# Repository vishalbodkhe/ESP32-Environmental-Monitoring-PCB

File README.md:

# ESP32 Environmental Monitoring PCB

A custom 2-layer PCB designed in KiCad for an ESP32-based environmental monitoring system.

## Features

- ESP32-WROOM-32
- DHT11 temperature and humidity sensor
- OLED I2C display
- LDR light sensor
- 5V USB power input
- AMS1117-3.3V regulation
- Reset and Boot buttons
- Power LED
- 4 × M3 mounting holes
- GND copper zone
- Custom PCB routing
- DRC verified
- Manufacturing-ready Gerber and drill files

## Hardware

| Component | Function |
|---|---|
| ESP32-WROOM-32 | Main Controller |
| DHT11 | Temperature & Humidity |
| LDR | Light Detection |
| OLED | I2C Display |
| AMS1117-3.3 | 5V to 3.3V Regulation |
| USB | Power Input |

## ESP32 Connections

| ESP32 Pin | Function |
|---|---|
| GPIO4 | DHT11 Data |
| GPIO21 | OLED SDA |
| GPIO22 | OLED SCL |
| GPIO34 | LDR ADC |
| GPIO0 | Boot |
| EN | Reset |

## Design Tools

- KiCad
- Schematic Editor
- PCB Editor
- 3D Viewer
- Gerber Viewer

## PCB Design

The PCB was designed as a 2-layer board with a dedicated GND copper zone, custom routing, antenna keep-out area and four M3 mounting holes.

## Manufacturing

Gerber and PTH/NPTH drill files are included for PCB manufacturing.

## Project Images

## Author

**Vishal Bodkhe**

Electronics & Computer Engineering

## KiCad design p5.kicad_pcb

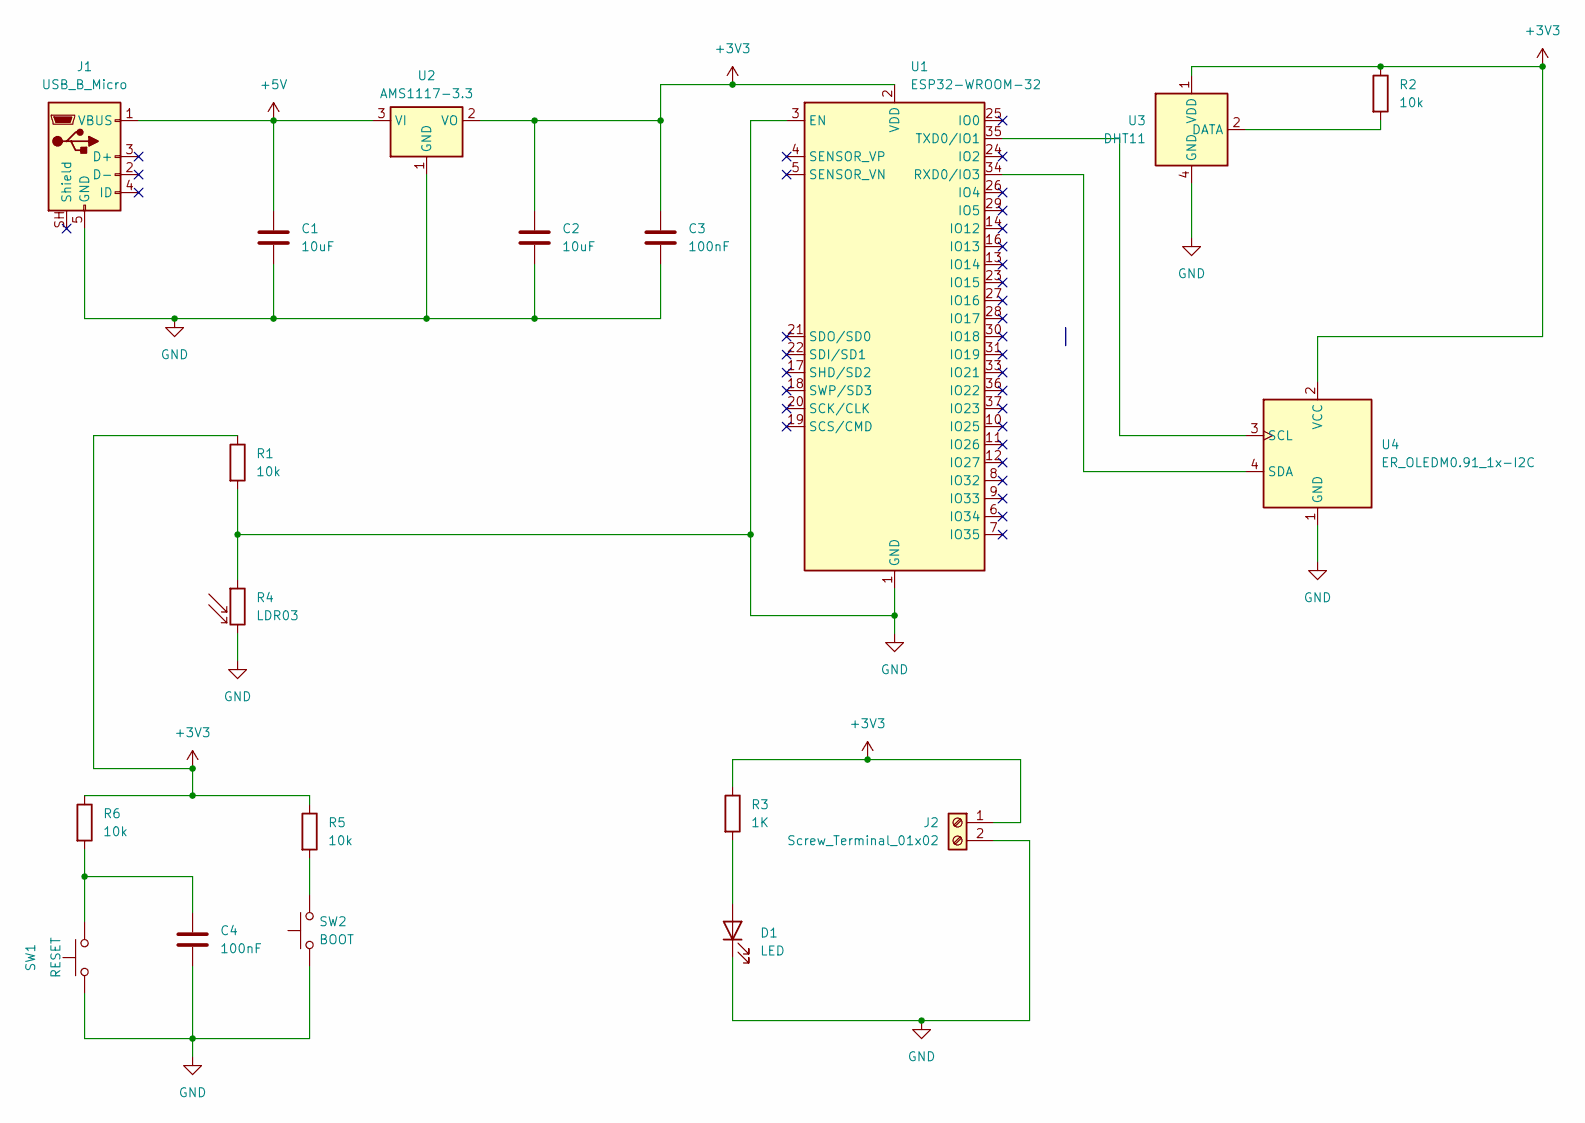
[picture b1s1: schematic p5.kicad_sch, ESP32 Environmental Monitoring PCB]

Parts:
C1, C2: 10uF; C_0805_2012Metric
C3, C4: 100nF; C_0805_2012Metric
D1: LED; LED_D5.0mm
J1: USB_B_Micro; USB_Micro-B_Molex-105017-0001
J2: Screw_Terminal_01x02; PinHeader_1x02_P2.54mm_Vertical
R1, R2, R5, R6: 10k; R_0805_2012Metric
R3: 1K; R_0805_2012Metric
R4: LDR03; R_LDR_10x8.5mm_P7.6mm_Vertical
SW1: RESET; SW_PUSH_6mm
SW2: BOOT; SW_PUSH_6mm
U1: ESP32-WROOM-32
U2: AMS1117-3.3; SOT-223-3_TabPin2
U3: DHT11; Aosong_DHT11_5.5x12.0_P2.54mm
U4: ER_OLEDM0.91_1x-I2C

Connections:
+3V3: C2.1, C3.1, J2.1, R1.1, R2.1, R3.1, R5.1, R6.1, U1.2 (VDD), U2.2 (VO), U3.1 (VDD), U4.2 (VCC)
+5V: C1.1, J1.1 (VBUS), U2.3 (VI)
GND: C1.2, C2.2, C3.2, C4.2, D1.1 (K), J1.5 (GND), J1.SH (Shield), J2.2, R1.2, R4.1, R4.2, SW1.1, SW2.1, U1.1 (GND), U1.3 (EN), U1.15 (GND), U1.38 (GND), U1.39 (GND), U2.1 (GND), U3.4 (GND), U4.1 (GND)
unnamed: C4.1, R6.2, SW1.2
unnamed: D1.2 (A), R3.2
unnamed: R5.2, SW2.2
unnamed: U1.34 (RXD0/IO3), U4.4 (SDA)
unnamed: U1.35 (TXD0/IO1), U4.3 (SCL)
unnamed: R2.2, U3.2 (DATA)

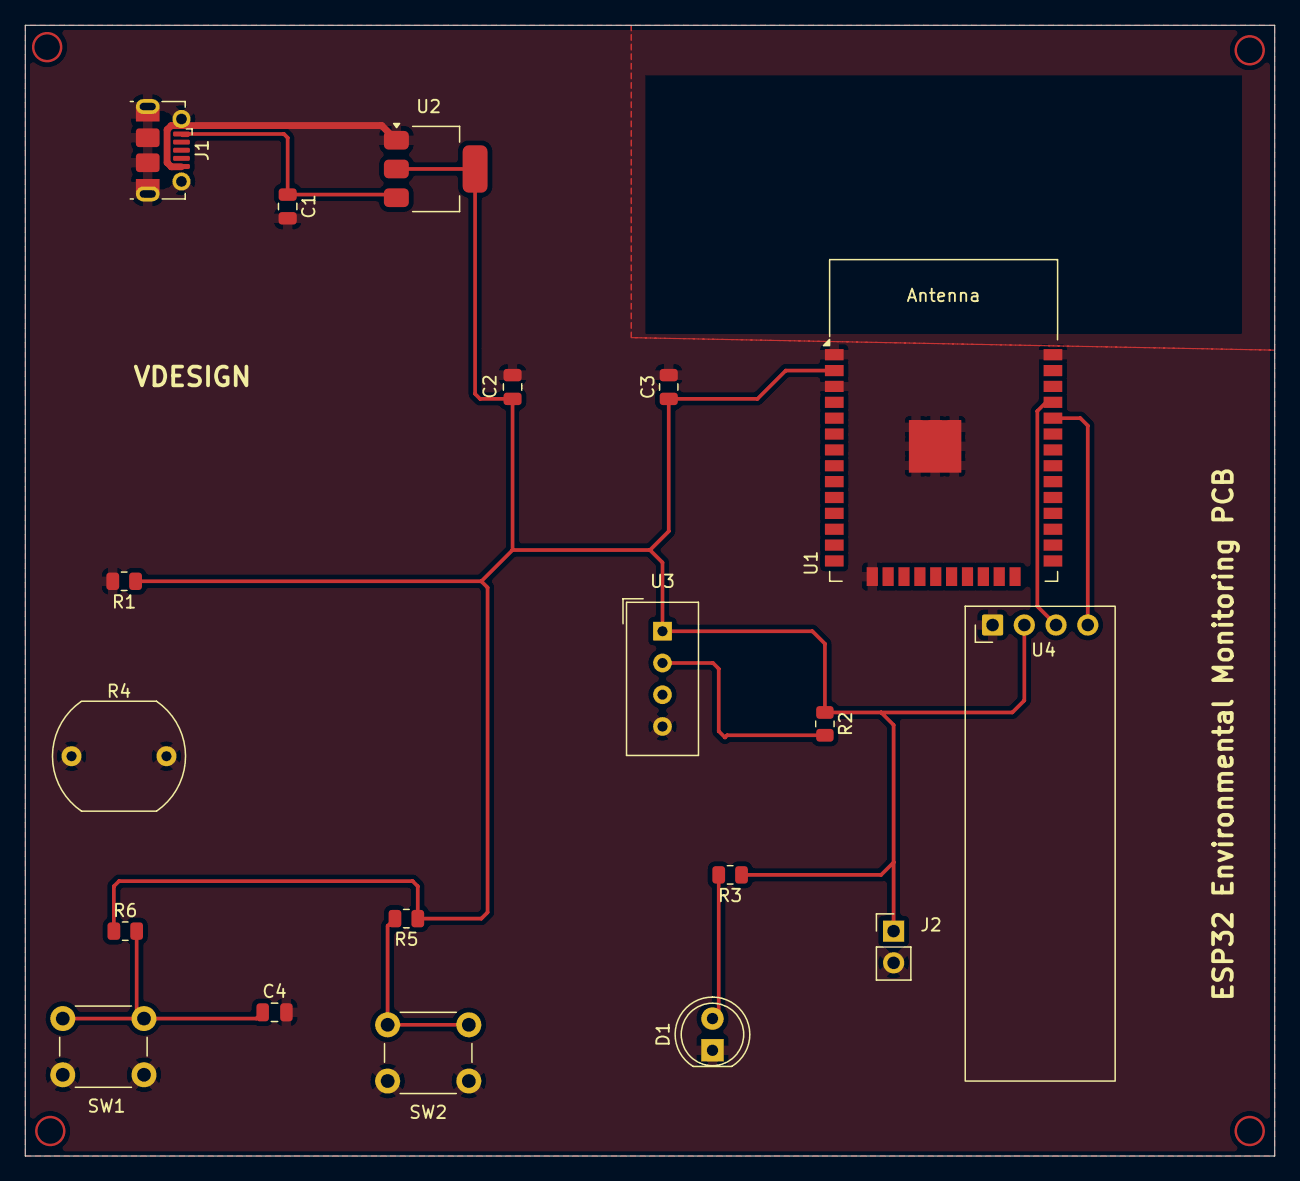
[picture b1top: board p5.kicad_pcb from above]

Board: 2 copper layers, 100.0 x 90.5 mm, 19 parts (0 on the bottom side), 9 nets.
